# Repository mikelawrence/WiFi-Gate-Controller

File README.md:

# Wireless Gate Controller
After years of using weak garage door openers and trying to position them just right so my solar powered gate 400' away would open when needed I decided it was time to make a wireless controller of my own. 802.11 is a ubiquitous choice and with the right antenna range is not a problem. Two wireless modules consistently popped up when searching for low power embedded WiFi, ESP8266 and ATWINC1500. In the end I chose the ATWINC1500 module for it's compatibility with Arduino and it's low power modes. This board is fully compatible with the Arduino MRK1000 which includes a SAMD21G18 Arm processor and the ATWINC1500 module. I also chose to use MQTT. Recent projects showed how effective the MQTT client/server model is in this situation. I use Home Assistant for home automation and it directly supports MQTT.

This board is designed for and tested with a US Automation Gate Opener.

This PCB design uses my custom libraries available here [Mike's KiCad Libraries](https://github.com/mikelawrence/KiCad-Libraries).

This PCB was designed with [KiCad 5.1.2](http://kicad.org).

_Note: The LMZ21700 Simple Switcher, SAMD21G18 ARM Processor, and ATWINC1500 WiFi Module have exposed pads on the bottom which requires either a reflow oven or hot air to solder properly._

For Bill of Materials generation I use my version of [KiBoM](https://github.com/mikelawrence/KiBoM) forked from [SchrodingersGat](https://github.com/SchrodingersGat/KiBoM).

## Status
* Rev 1.1 PCB has been updated to support KiCad 5.1 libraries. Some footprints changed when libraries were updated but changes were minimal. This board has NOT been tested.
  * Order the PCB from [OSH Park](https://oshpark.com/shared_projects/2w66ZpSF).
  * Order the parts from Mouser using this [Shared BOM](https://www.mouser.com/ProjectManager/ProjectDetail.aspx?AccessID=595b0bc14b).
* Rev 1.0 PCB has been been ordered, assembled, and tested. Hardware is fully operational.
  * Order the PCB from [OSH Park](https://oshpark.com/shared_projects/rpQhhUss).
  * Order the parts from Mouser using this [Shared BOM](https://www.mouser.com/ProjectManager/ProjectDetail.aspx?AccessID=595b0bc14b).

## Board Preview

## Design
### Input Power
All components are powered by a 3.3VDC Simple Switcher from Texas Instruments (LMZ21700). Input power is 12VDC nominal with a range of 5V-17V. The with the switching power supply efficiency at about 80% the board current draws at the lowest 5mA and an average around 12mA. Peak current during transmit is about 100mA.

### Contact Inputs
Contact inputs use a simple pull-up to 5VDC and a Schmidt Trigger Inverter (SN74LVC2G14). Note: software debounce is still required. A high value pull-up resistor and series resistor (both 100k) were selected to reduce current levels when accidental high voltages are applied to the input. The resistor pull-ups should be installed where needed. If connecting to a gate controller that already has an input pulled up leave the pull-up resistors off. The inputs are 5V tolerant. ESD Protection devices are included to further protect the inputs. Due to the Schmidt Trigger Inverter the software sees a logic high when a contact is closed (shorted to -V).

### Contact Outputs
There are four contact outputs on the board which short to ground (-V) when activated. The switch is an overload protected Infineon Low-Side Automotive Switch (BTS3800SL). Each contact output has input circuitry identical to the contact inputs on the board. This allows detection of external contact closures for parallel wired contacts.

### SAMD ARM Processor and WiFi Module
The ARM processor and ATWINC1500 WiFi module are wired identical to the MKR1000 Arduino board, thus the Arduino development environment is used for software development and the ATWINC1500 module is directly supported.

## Setup
### Arduino Setup
This board is designed to mimic a [MKR1000](https://store.arduino.cc/usa/arduino-mkr1000) board from Arduino. Make sure the the MKR1000 board is supported by installing . Do this by opening the Board Manager as shown below.

Type in "samd" in the filter edit and you will see several options. Select "Arduino SAMD Boards (32-bits ARM Cortex-M0+)" and install the latest version as shown below.

It will take a few minutes to download and install the board package. Once complete it's time to install the necessary libraries. Start by opening the Library Manager as shown below.

Type in "mqtt" in the filter edit and scroll down until you see "MQTT by Joel Gaehwiler" as shown below.

Once "MQTT" is installed repeat the install for the following libraries.

* WiFi101 by Arduino
* WiFiOTA by Arduino
* OneWire by Paul Stoffregen and many others
* DallasTemperature by Miles Burton and others

### Board Setup
The Arduino development environment expects a bootloader in the SAMD ARM processor which will allow programming via USB. The bootloader must be programmed first using a supported programming pod. I used an "Atmel-ICE" pod but there are other options. First make sure you have selected the "Arduino/Genuino MKR1000" board as shown below.

Next select your programmer.

Make sure the board is powered via USB and the programmer is connected to the debug connector then select "Burn Bootloader".

Now the bootloader is programmed it's time to load the "WiFi101 FirmwareUpdater" example. This will update the firmware in the ATWINC1500 module.

Now "Upload" the "WiFi101 FirmwareUpdater" example.

Update the ATWINC1500 module by selecting "WiFi101 Firmware Updater".

Click the "Update Firmware" button.

Finally open the "WiFi_Gate_Controller.ino" sketch downloaded from GitHub. Update the necessary defines for your Wireless network and MQTT server settings see the [Code README](code/README.md) for more information. Now upload it just like the "WiFi101 FirmwareUpdater" example. All done!

# Acknowledgments
[Arduino](www.arduino.cc) kindly develops open source hardware and software which makes writing software for the board incredibly easy.

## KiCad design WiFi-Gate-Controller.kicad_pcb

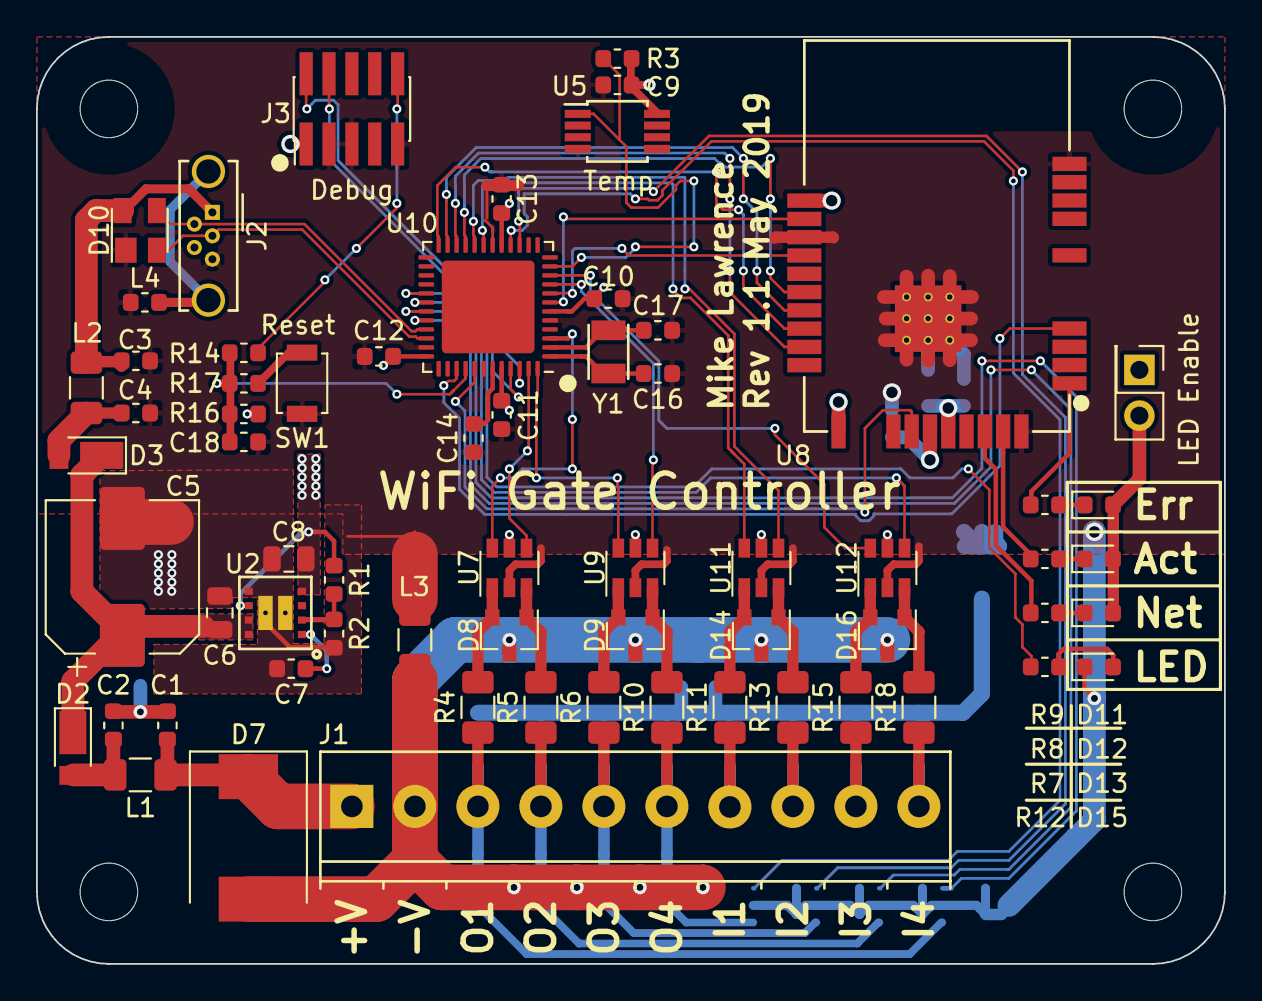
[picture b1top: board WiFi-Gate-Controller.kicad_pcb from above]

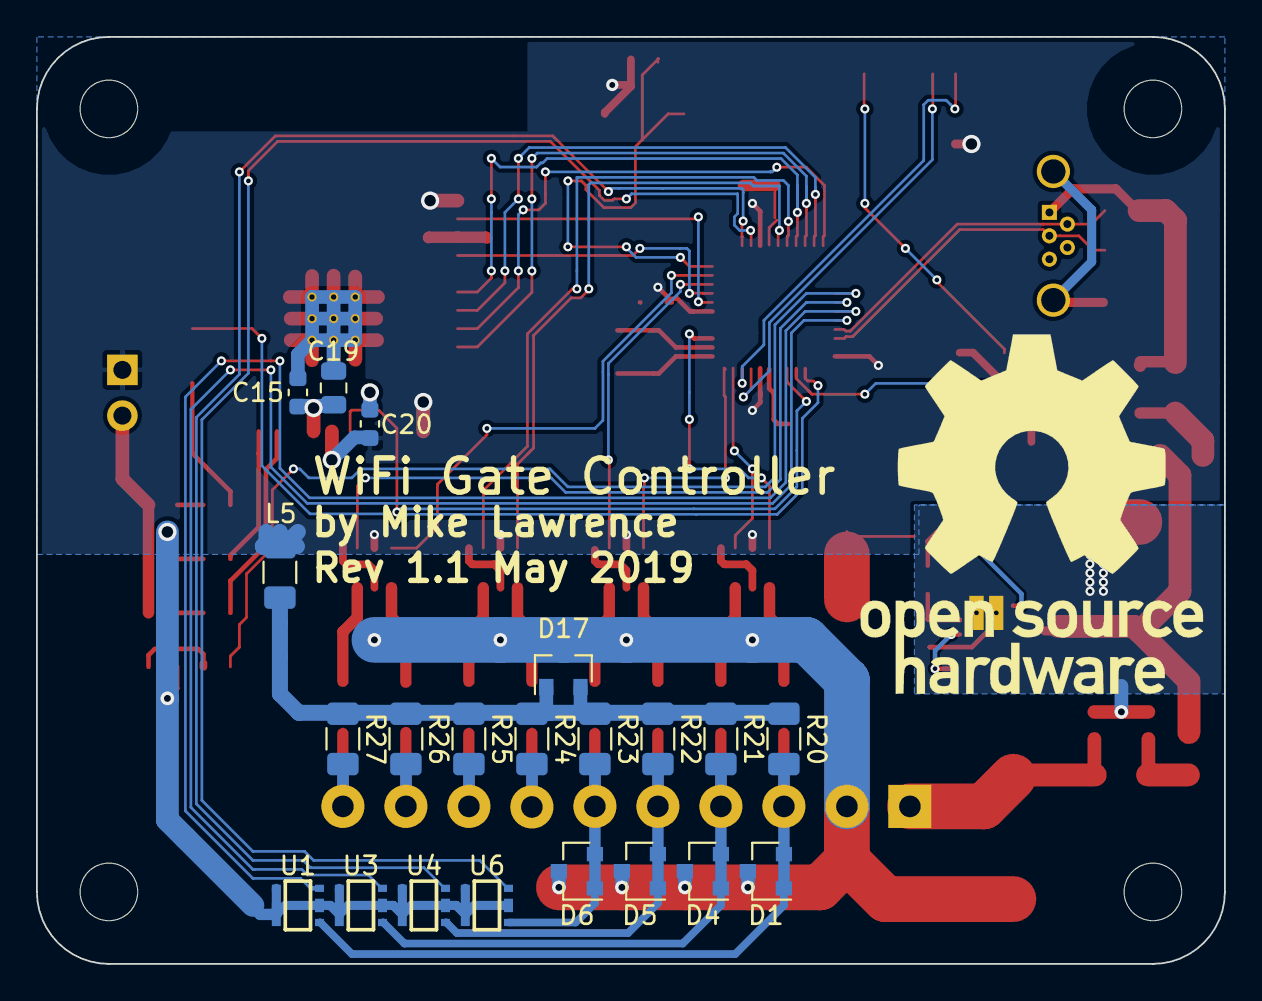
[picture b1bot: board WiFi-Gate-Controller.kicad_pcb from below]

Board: 2 copper layers, 66.0 x 51.5 mm, 86 parts (21 on the bottom side), 69 nets.

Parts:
C1, C2, C3, C4: 1000pF; C_0603_1608Metric
C5: 100uF; CP_Elec_8x10
C6, C8, C19: 22uF; C_0805_2012Metric
C7: 3300pF; C_0603_1608Metric
C9, C10, C11, C12, C13, C15, C18: 0.1uF; C_0603_1608Metric
C14, C20: 1uF; C_0603_1608Metric
C16, C17: 15pF; C_0603_1608Metric
D1, D4, D5, D6: NUP2105L; SOT-23
D2, D3: DFLS130; D_PowerDI-123
D7: SM15T33CA; D_SMC
D8, D9, D14, D16, D17: TPD2E2U06; SOT-23
D10: PRTR5V0U2X; SOT-143
D11: Red; LED_0603_1608Metric
D12: Yellow; LED_0603_1608Metric
D13: Green; LED_0603_1608Metric
D15: Orange; LED_0603_1608Metric
J1: Screw_Terminal_01x10; TerminalBlock_Phoenix_PT-3.5mm_10pol
J2: USB_B_Micro; USB_Micro-B_Wuerth_614105150721_Vertical_CircularHoles
J3: Cortex Debug; PinHeader_2x05_P1.27mm_Vertical_SMD
JP1: LED Disable; PinHeader_2x01_P2.54mm_Vertical
L1, L2, L3, L5: 1k@100MHz; L_1206_3216Metric
L4: 470@100MHz; L_0603_1608Metric
R1: 1.21M; R_0603_1608Metric
R2: 383k; R_0603_1608Metric
R3: 4.7k; R_0603_1608Metric
R4, R5, R6, R10, R11, R13, R15, R18, R20, R21, R22, R23, R24, R25, R26, R27: 100k; R_1206_3216Metric
R7, R8, R9, R12: 1k; R_0603_1608Metric
R14: 39R; R_0603_1608Metric
R16: 10k; R_0603_1608Metric
R17: 330R; R_0603_1608Metric
SW1: Reset; SW_SPST_B3U-1000P
U1, U3, U4, U6: BTS3800SL; Infineon_PG-SCT595-5-1
U2: LMZ21700; Converter_DCDC_Texas-SIL0008E
U5: DS18B20U; MSOP-8_3x3mm_P0.65mm
U7, U9, U11, U12: 74LVC2G14; SOT-23-6
U8: ATWINC1500-MR210UB; Microchip_ATWINC1500-MR210UB
U10: SAMD21G18-M; QFN-48-1EP_7x7mm_P0.5mm_EP5.15x5.15mm
Y1: 32.768kHz; Crystal_SMD_Abracon_ABS07-2Pin_3.2x1.5mm

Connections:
+3V3: C8.1, C9.2, C10.2, C11.2, C12.2, C13.2, C20.2, J3.1, JP1.1, L5.1, R1.1, R3.1, R16.2, U2.4, U2.6, U5.8, U7.5, U8.10, U8.20, U8.23, U9.5, U10.6, U10.17, U10.36, U10.44, U11.5, U12.5
+BATT: C1.2, D7.1, J1.1, L1.1
/A0: U7.6, U10.3
/A1: U7.4, U10.47
/A2: U9.6, U10.48
/A3: U9.4, U10.9
/A4: U10.10, U12.6
/A5: R3.2, U5.1, U10.11
/D0: U1.3, U10.31
/D1: U3.3, U10.32
/D2: U4.3, U10.15
/D3: U6.3, U10.16
/D4: U10.19, U11.6
/D5: U10.20, U11.4
/D6: R12.1, U10.29
/D7: U10.30, U12.4
/SWCLK: J3.4, U10.45
/SWDIO: J3.2, U10.46
/USB_N: D10.3, J2.2, U10.33
/USB_P: D10.2, J2.3, U10.34
/WINC_EN: U8.22, U10.41
/WINC_MISO: U8.17, U10.24
/WINC_MOSI: U8.15, U10.21
/WINC_SCK: U8.18, U10.22
/WINC_WAKE: U8.11, U10.7
/~RESET~: C18.2, R14.1, R16.1, R17.1, U10.40
/~WINC_IRQ: U8.13, U10.8
/~WINC_RST: U8.4, U10.39
/~WINC_SS: U8.16, U10.23
GND: C1.1, C2.1, C3.1, C4.1, C5.2, C6.2, C7.2, C8.2, C9.1, C10.1, C11.1, C12.1, C13.1, C14.1, C15.1, C16.1, C17.1, C18.1, C19.2, C20.1, D10.1, D15.1, J2.5, J3.3, J3.5, J3.9, L3.2, L4.1, R2.2, SW1.2, U1.2, U1.4, U1.5, U2.5, U2.9, U2.10, U3.2, U3.4, U3.5, U4.2, U4.4, U4.5, U5.4, U6.2, U6.4, U6.5, U7.2, U8.9, U8.12, U8.28, U8.29, U9.2, U10.5, U10.18, U10.35, U10.42, U11.2, U12.2
GNDPWR: D1.3, D4.3, D5.3, D6.3, D7.2, D8.3, D9.3, D14.3, D16.3, D17.3, J1.2, L3.1
unnamed: C2.2, D2.2, L1.2
unnamed: C4.2, D3.2, L2.2
unnamed: C5.1, C6.1, D2.1, D3.1, U2.7, U2.8
unnamed: C7.1, U2.1
unnamed: C14.2, U10.43
unnamed: C15.2, C19.1, U8.24
unnamed: C16.2, U10.1, Y1.1
unnamed: C17.2, U10.2, Y1.2
unnamed: D1.1, D1.2, J1.3, R4.1, R20.2, U1.1
unnamed: D4.1, D4.2, J1.4, R5.1, R21.2, U3.1
unnamed: D5.1, D5.2, J1.5, R6.1, R22.2, U4.1
unnamed: D6.1, D6.2, J1.6, R10.1, R23.2, U6.1
unnamed: D8.1, R5.2, U7.3
unnamed: D8.2, R4.2, U7.1
unnamed: D9.1, R10.2, U9.3
unnamed: D9.2, R6.2, U9.1
unnamed: D11.1, R9.2
unnamed: D11.2, D12.2, D13.2, JP1.2
unnamed: D12.1, R8.2
unnamed: D13.1, R7.2
unnamed: D14.1, R13.2, U11.3
unnamed: D14.2, R11.2, U11.1
unnamed: D15.2, R12.2
unnamed: D16.1, R18.2, U12.3
unnamed: D16.2, R15.2, U12.1
unnamed: D17.1, D17.2, L5.2, R20.1, R21.1, R22.1, R23.1, R24.1, R25.1, R26.1, R27.1
unnamed: J1.7, R11.1, R24.2
unnamed: J1.8, R13.1, R25.2
unnamed: J1.9, R15.1, R26.2
unnamed: J1.10, R18.1, R27.2
unnamed: J2.6, L4.2
unnamed: J3.10, R14.2
unnamed: R1.2, R2.1, U2.2
unnamed: R7.1, U8.26
unnamed: R8.1, U8.27
unnamed: R9.1, U8.1
unnamed: R17.2, SW1.1
VBUS: C3.2, D10.4, J2.1, L2.1

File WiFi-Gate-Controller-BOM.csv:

Quantity,References,Description,Manufacturer,Part Number,Vendor,Vendor Part Number
4,C1 C2 C3 C4,"CAP, 0603, 1000pF, 10%, X7R, 10V",Vishay,VJ0603Y102KXAAC31,Mouser,77-VJ0603Y102KXAAC31
1,C5,"CAP, SMD 8X10, 20%, EC, 35V",United Chemi-Con,EMVH350ADA101MHA0G,Mouser,661-EMVH350ADA101M
3,C6 C8 C19,"CAP, 0805, 22uf, 20%, X5R, 25V",Taiyo Yuden,TMK212BBJ226MG-TT,Mouser,963-TMK212BBJ226MGTT
1,C7,"CAP, 0603, 3300pF, 5%, X7R, 10V",Vishay,VJ0603Y332JXQPW1BC,Mouser,77-VJ0603Y332JXQPBC
7,C9 C10 C11 C12 C13 C15 C18,"CAP, 0603, 0.1uF, 20%, X7R, 10V",Vishay,VJ0603Y104JXQPW1BC,Mouser,77-VJ0603Y104JXQPBC
2,C14 C20,"CAP, 0603, 1uF, 10%, X7R, 10V",AVX,0603ZC105JAT2A,Mouser,581-0603ZC105JAT2A
2,C16 C17,"CAP, 0603, 15pF, 5%, C0G, 50V",AVX,06035A150JAT2A,Mouser,581-06035A150J
4,D1 D4 D5 D6,"TVS, SOT23, ESD Protection, CAN, 24V",ON Semiconductor,SZNUP2105LT1G,Mouser,863-SZNUP2105LT1G
2,D2 D3,"DIO, PowerDI123, Schottky Rectifier, 30V, 1A",Diodes Inc,DFLS130LQ,Mouser,621-DFLS130L
1,D7,"TVS, SMC, Transil, 1500W, 33V",ST Micro,SM15T33CA,Mouser,511-SM15T33CA
5,D8 D9 D14 D16 D17,"TVS, SOT23, ESD TVS Protection, Dual",Texas Instruments,TPD2E2U06QDBZRQ1,Mouser,595-TPD2E2U06QDBZRQ1
1,D10,"TVS, SOT23, ESD Protection, USB",Nexperia,"PRTR5V0U2X,215",Mouser,771-PRTR5V0U2X-T/R
1,D11,"LED, 0603, Red",Lumex,SML-LX0603SRW-TR,Mouser,696-SML-LX0603SRW
1,D12,"LED, 0603, Yellow",Lumex,SML-LX0603SYW-TR,Mouser,696-SML-LX0603SYW
1,D13,"LED, 0603, Green",Lumex,SML-LX0603SGW-TR,Mouser,696-SML-LX0603SGW
1,D15,"LED, 0603, Orange",Lumex,SML-LX0603SOW-TR,Mouser,696-SML-LX0603SOW
1,J1,"CON, THT, Terminal Block, Pluggable, 3.5mm, 10 Pos",Phoenix,1731565,Mouser,651-1731565
1,J2,"CON, THT, Micro USB 2.0 Type AB, Vertical",Wurth Electronics,614105150721,Mouser,710-614105150621
1,J3,"CON, SMD, 1.27mm Header, Dual Row, Vertical, 10 Pos",Amphenol FCI,202112100010C4LF,Mouser,649-202112100010C4LF
1,JP1,"CON, THT, 2.54mm Header, Single Row, Vertical, 2 Pos",Molex,22-03-2021,Mouser,538-22-03-2021
4,L1 L2 L3 L5,"BEAD, 1206, 1k@100MHz, 2A",Murata,BLM31KN102SH1L,Mouser,81-BLM31KN102SH1L
1,L4,"BEAD, 0603, 470R@100MHz, 1A",Murata,BLM18PG471SN1D,Mouser,81-BLM18PG471SN1D
1,R1,"RES, 0603, 1.21M, 1%, T100",Yageo,RC0603FR-071M21L,Mouser,603-RC0603FR-071M21L
1,R2,"RES, 0603, 383k, 1%, T100",Panasonic,ERJ-3EKF3833V,Mouser,667-ERJ-3EKF3833V
1,R3,"RES, 0603, 4.7k, 1%, T100",Panasonic,ERJ-3EKF4701V,Mouser,667-ERJ-3EKF4701V
16,R4 R5 R6 R10 R11 R13 R15 R18 R20 R21 R22 R23 R24 R25 R26 R27,"RES, 1206, 100k, 5%, T200",Panasonic,ERJ-P08J104V,Mouser,667-ERJ-P08J104V
4,R7 R8 R9 R12,"RES, 0603, 1k, 1%, T100",Panasonic,ERJ-3EKF1001V,Mouser,667-ERJ-3EKF1001V
1,R14,"RES, 0603, 39R, 1%, T100",Panasonic,ERJ-3EKF39R0V,Mouser,667-ERJ-3EKF39R0V
1,R16,"RES, 0603, 10k, 1%, T100",Panasonic,ERJ-3EKF1002V,Mouser,667-ERJ-3EKF1002V
1,R17,"RES, 0603, 330R, 1%, T100",Panasonic,ERJ-3EKF3300V,Mouser,667-ERJ-3EKF3300V
1,SW1,"SW, SMD, Push Button",Omron,B3U-1000P,Mouser,653-B3U-1000P
4,U1 U3 U4 U6,"IC, SCT595, Smart Low Side Switch, 41V, 350mA",Infineon,BTS3800SL,Mouser,726-BTS3800SL
1,U2,"MODULE, SMD, Simple Switcher, 17V, 650mA",TI,LMZ21700SILR,Mouser,595-LMZ21700SILR
1,U5,"IC, MSOP8, 1-Wire Temperature Sensor",Maxim,DS18B20U+,Mouser,700-DS18B20U
4,U7 U9 U11 U12,"IC, SOT23-6, Dual inverting Schmitt trigger",Texas Instruments,SN74LVC2G14DBVG4,Mouser,595-SN74LVC2G14DBVG4
1,U8,"MODULE, SMD, WiFi, u.FL connector",Atmel,ATWINC1500-MR210UB1140,Mouser,579-C1500MR210UB1140
1,U10,"IC, QFN44, MCU, ARM, 256kB Flash, 32kB SRAM, 48MHz",,ATSAMD21G18A-MUT,Mouser,556-ATSAMD21G18A-MUT
1,Y1,"XTL, SMD, 32.768kHz",Abracon,ABS07-32.768KHZ-9-T,Mouser,815-ABS07-32.768K9T





Component Groups:,38
Component Count:,86
Fitted Components:,86
Number of PCBs:,1
Total components:,86
Schematic Version:,1.1
Schematic Date:,May 2019
BoM Date:,"Thursday, May 16, 2019 at 06:02:52 PM"
Schematic Source:,/Users/mike/Documents/KiCad/WiFi-Gate-Controller/WiFi-Gate-Controller.sch
KiCad Version:,Eeschema (5.1.2-1)-1

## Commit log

2018-05-15 Changed file names to be more consistent.
2018-05-15 Removed relative link to pdfs that don't work.
2018-05-15 Added code README.
2018-05-15 Minor corrections in the README file.
2018-05-18 Rename Arduino project. README updates. Added status section to software README.
2018-05-22 Corrections to README's.
2018-05-22 Still fixing errors in README's.
2018-05-28 Update LED indication
    LED is turned on when a command input is active instead of command output. Fixed some compilere warnings.
2018-05-31 Upped Version to 0.2. Added WiFi reconnect cycle. Added Print() and Println() defines. Watchdog Timeout changed.
    WiFi will now attempt a reconnect when it has been disconnected for too long. Println() and Print() defines embed the ENABLE_SERIAL define making code look cleaner. Watchdog Timeout set to 64 seconds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
2018-06-03 Cleanup ifdef ENABLE_SERIAL in program. Fixed temperature publishing to prevent a series of catchup publishes if the MQTT server was offline.
2018-06-03 Match actual description in previous commit.
2018-06-11 Upped version to 0.3. Improved WiFi reliablity.
    Sometime WIFi looses access to network without showing disconnected in status. To get around this timeout on MQTT connect retries was added. This stops the WiFi connection so it can reconnect.
2018-06-12 Upped version to 0.3. Added automatic support for testing on other boards.
    Updated status in README.
2018-07-31 Update to KiCad 5.0.0. Remove unecessary files.
2018-08-21 Update Status in README.
2018-11-28 Update WiFi101 library.
    Update WiFi101 library to 0.15.3. Version to 0.4.
2019-03-03 Arduino IDE 1.8.8, updated WINC1500 firmware to 19.6.1.
2019-05-05 Update to KiCad 5.1 libraries.
    Also updated custom libraries.
2019-05-05 Edit README
2019-05-11 Remove unnecessary gerbers. Update gerber generation settings.
2019-05-21 Arduino library updates.
    Cleanup BOM.
    Support KiBom.
2019-06-05 Minor formatting cleanup.
2019-06-29 Move project defines to separate h file.
2021-03-28 Add Home Assistant device support
    The Gate Controller will now show up as a device under mqtt integration. All entities will be associated with the device. Unique_id comes from SAMD21 processor serial.
2021-04-04 New device branch
    Breakout MQTT options into separate commands.
    Minor formatting.
2021-04-04 Revert to more stable code
    Recent changes to the add Home Assistant device information to the MQTT topics caused instability. This is probably related to String library usage. The changes that caused problems are now in the de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
2021-04-04 Change MQTT options
2021-11-08 Update Kicad link.
